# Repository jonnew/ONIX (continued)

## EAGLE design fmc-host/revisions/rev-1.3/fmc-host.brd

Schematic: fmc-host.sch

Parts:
AUX: 12226-8250-00FR; 12226-82X0-00XX
C1, C2, C47, C52, C57, C63, C85, C86, C94, C95, C99, C101, C102, C107, C109, C110, C111, C112, C113, C117, C118, C119: 10uF; 0805
C3, C4, C25, C26, C50, C51, C55, C56, C58, C59, C61, C62, C68, C73, C74, C81, C82, C90, C91, C114, C115, C116: 10nF; 0402
C5, C6, C12, C13, C14, C15, C16, C17, C18, C19, C20, C21, C22, C23, C24, C31, C32, C33, C34, C35, C36, C39, C42, C43, C44, C45, C46, C53, C54, C64, C65, C66, C71, C72, C75, C76, C77, C79, C80, C83, C87, C88, C92, C93, C96, C97, C98, C100, C103, C104, C105, C108, C123, C124, C125, C127, C128, C130, C131: 0.1uF; 0402
C7, C29, C30: 4.7nF; 0402
C8, C9, C10, C11, C27, C28, C37, C38, C48, C49, C67, C69, C70, C132, C133: 4.7uF; 1206
C40, C41: 47nF; 0402
C60, C78: 1uF; 0805
C84, C89, C120, C121, C122, C126, C129: 47uF; 1210
C106: 100pF; 0402
CLKI0, CLKI1: SMA002; MMCX-THRU
CLKO: SMA002; MMCX-THRU
D1, D2, D3: LED_0402; LED-0402
D4, D5: SESD0402X1UN-0020-090; 0402P-DFN
D6, D7, D8: BAR66; SOT23
D9: KDZ4.3B; SOD123
D10, D11: APFA3011-AK13/F; RGB_LED_SMD-6
F1, F2, F3: C014F-2; 1812
J6: PINHD-2X5_ESHF-SM; ESHF-105-01-L-D-SM-K-TR
J8: PINHD-2X8_SMD; JP2X8_SMD
J9: FMC_SINGLE_WIDTH_MODULE
J10: ASP-134488-01; FMC_HPC_MALE
L1, L2: 1008PS-472; 1008PS
L3, L4, L7, L8, L11, L12: BLM18KG601SN1D; 0603
L5, L6: SRNxx-101M; SRN6045TA
L9, L10: MPZ2012S102AT000; 0805
L13, L14, L15, L16, L17, L18: BLM15PX601SN1D; 0402; PARTNO BLM15PX601SN1D
LINKA: SMA002; MMCX-THRU
LINKB: SMA002; MMCX-THRU
Q1, Q2, Q3, Q4: SI1012R; SC75
R1: 1.6k; 0402
R2, R3: 3.9k; 0402
R4, R5, R29, R31, R45, R56, R61: 3k; 0402
R6, R7, R24, R25, R28, R30, R39, R40, R41, R42, R43, R44, R74, R79, R80, R81, R83, R84, R95, R96: 10k; 0402
R8, R9, R10, R11, R18, R19, R26, R27, R48, R49, R50, R51, R62, R63, R64, R65, R66, R67: 1k; 0402
R12, R13, R22, R23, R93: 165k; 0402
R14, R15, R16, R17, R20, R21: 150,0.25W; 0603
R32, R33: 60 1%; 0402
R34, R35, R46, R47: 49.9; 0402
R36, R37, R38: 100; 0402
R52, R54, R57, R59: DNP; 0402
R53, R55, R58, R60, R78, R82: 0; 0402
R68, R69, R70, R71: 2.2k; RN2X8-1506
R72, R73, R91, R92: 2k; 0402
R75, R76: 3.16k; 0402
R77: 649k; 0402
R85: 15k; 0402
R86, R88, R90: 4.7k; 0402
R87, R89: 43k; 0402
R94: 178k; 0402
R97, R98: 73.2k; 0402
S1, S2: CHS-01TA; DIP01-SMD-GULL
S3: CHS-02TB
SJ1, SJ2: SJ2_0201; SJ_2_0201
TP1, TP2, TP4, TP5, TP6, TP7, TP11, TP12, TP13, TP14, TP15, TP16: TPB1,27; B1,27
TP3, TP8, TP9, TP10, TP17, TP18: TPB2,54; B2,54
U1: NC7WZ07P6X; SC70
U2: SN65LVDS9638DGN; MSOP-8-PAD-3X3
U3: FIN1032MTCX; TSSOP-16
U4: LTC2875_DFN; DFN83X3
U5, U6: ADCMP600; SOT-23-5
U7, U8, U9: ADG1434YCPZ; QFN20-4X4MM
U10, U11: DS90UB914A-Q1; WQFN48-7.4X7.4
U12: DS91M040; WQFN32-5X5
U13: AD5766BCPZ-RL7; CP_40_7
U14: MCP47FEB02A0-E/ST; TSSOP-8
U15: LM4132AMF-2.5/NOPBCT-ND; SOT-23-5
U16: AD7617BSTZ; ST_80_2
U17: AD5142BCPZ10; CP_16_27-L
U18: LTM4622A; BGA_5X5_625X625
U19, U20: TPS7A49; PVSON-N8+4-3X3
U21: TPS7A30; PVSON-N8+4-3X3
U22: 24AA64ST; TSSOP8
U23: LTM8049_BGA; LTM8049
X2, X3: OE-LOGO_7X5; OE-LOGO-7X5

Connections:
!ADC_CS: J10.H13 (LA07_P), U16.63 (!CS)
!ADC_RESET: C106.1, J10.F10 (HA08_P), R81.2, U16.36 (!RESET)
!AIN_AOUT_EN: J10.J19 (HA18_N), U7.18 (!EN), U8.18 (!EN), U9.18 (!EN)
!DAC_CS: J10.J16 (HA14_N), U13.8 (!CS)
!DAC_RESET: J10.F14 (HA12_N), U13.3 (!RESET)
!LINK_PWR_ADJ_CS: J10.F38 (HB20_N), U17.14 (!CS)
!LINK_PWR_ADJ_RESET: J10.E37 (HB21_N), U17.16 (!RESET)
$N1: D8.3 (COMM), F2.2, R5.2, R15.2, R17.2, R21.2, R35.1
$N2: D6.3 (COMM), F3.2, U1.4 (OUT2), U1.6 (OUT1)
$N3: D7.3 (COMM), F1.2, R4.2, R14.2, R16.2, R20.2, R34.1
+1V8: C73.2, C74.2, C76.2, C77.2, C81.2, C82.2, C87.2, C88.2, C90.2, C91.2, C96.2, C97.2, C129.2, C130.2, C131.2, J10.E39 (VADJ), J10.F40 (VADJ), J10.G39 (VADJ), J10.H40 (VADJ), L3.2, L4.2, L7.2, L8.2, L11.1, L12.1, R28.1, R30.1, R52.1, R54.1, R57.1, R59.1, TP16.TP, U10.3 (VDDSSCG), U10.17 (VDDD), U10.36 (VDDR), U11.3 (VDDSSCG), U11.17 (VDDD), U11.36 (VDDR)
+3V3: C15.2, C23.1, C24.1, C29.1, C30.1, C35.1, C36.1, C39.1, C45.2, C46.2, C50.2, C51.2, C55.2, C56.2, C60.2, C61.2, C62.2, C64.2, C65.2, C66.2, C68.2, C69.2, C70.2, C79.2, C83.2, C86.2, C104.2, C107.2, C108.2, C110.2, C126.2, C127.2, C128.2, C132.1, C133.1, J10.C39 (3P3V1), J10.D36 (3P3V2), J10.D38 (3P3V3), J10.D40 (3P3V4), R6.1, R7.1, R41.2, R42.2, R43.2, R44.2, R48.2, R49.2, R50.2, R51.2, R72.2, R73.2, R78.1, R79.1, R80.1, R81.1, R95.2, R96.2, S1.2, S2.2, TP11.TP, U1.5 (VCC), U2.1 (VCC), U3.4 (EN), U3.16 (VCC), U4.3 (VCC), U5.5 (V+), U6.5 (V+), U10.7 (VDDIO3), U10.20 (VDDIO2), U10.29 (VDDIO1), U11.7 (VDDIO3), U11.20 (VDDIO2), U11.29 (VDDIO1), U12.11 (VDD), U12.12 (VDD), U12.29 (VDD), U12.30 (VDD), U13.4 (VLOGIC), U14.1 (VDD), U14.2 (REFA), U16.49 (VDRIVE), U17.9 (VDD), U17.10 (VLOGIC), U17.15 (INDEP), U23.A5 (VIN1), U23.A6 (VIN1), U23.A7 (VIN1), U23.B7 (RUN1), U23.K7 (RUN2), U23.L5 (VIN2), U23.L6 (VIN2), U23.L7 (VIN2)
+5V_AN: C47.2, C52.2, C57.2, C63.2, C67.1, C71.2, C72.2, C75.2, C80.2, C100.2, C101.2, L13.1, R1.2, TP1.TP, U13.28 (AVCC), U15.3 (EN), U15.4 (VIN), U16.6 (VCC), U16.15 (VCC), U16.30 (VCC), U16.71 (VCC)
+12V: AUX.1, AUX.26, C109.2, C120.2, C123.2, C124.2, J10.C35 (12P0V1), J10.C37 (12P0V2), R56.2, R61.2, TP12.TP, U18.A2 (VIN), U18.B3 (VIN), U18.D3 (VIN), U18.E2 (VIN)
+13V_AN: C12.2, C13.2, C14.2, C98.2, C99.2, L14.1, R2.2, TP2.TP, U7.13 (V+), U8.13 (V+), U9.13 (V+), U13.26 (AVDD)
+15V: C121.2, L16.2, L17.2, R93.1, U23.A1 (VOUT1P), U23.A2 (VOUT1P), U23.B1 (VOUT1P), U23.B2 (VOUT1P)
-13V_AN: C20.2, C21.2, C22.2, C92.2, C95.2, L15.1, R3.2, TP4.TP, U7.3 (V-), U7.PAD (V-), U8.3 (V-), U8.PAD (V-), U9.3 (V-), U9.PAD (V-), U13.6 (AVSS), U13.PAD (AVSS)
-15V: C122.1, L18.2, R94.1, U23.G1 (VOUT2N), U23.G2 (VOUT2N), U23.H1 (VOUT2N), U23.H2 (VOUT2N), U23.J2 (VOUT2N)
ADC_BUSY: J10.J12 (HA11_P), U16.67 (BUSY)
ADC_CONVST: J10.K13 (HA10_P), U16.68 (CONVST)
ADC_MISO_A: J10.K11 (HA06_N), U16.57 (DB12/SDOA)
ADC_MISO_B: J10.J10 (HA07_N), U16.56 (DB11/SDOB)
ADC_MOSI: J10.K10 (HA06_P), U16.55 (DB10/SDI)
ADC_SCLK: J10.J13 (HA11_N), U16.62 (SCLK/!RD)
ADDR0: J10.C27 (LA27_N), R95.1, S3.4
ADDR1: J10.C26 (LA27_P), R96.1, S3.3
AGND: AUX.13, AUX.14, C12.1, C13.1, C14.1, C20.1, C21.1, C22.1, C47.1, C52.1, C57.1, C63.1, C67.2, C71.1, C72.1, C75.1, C78.1, C80.1, C85.1, C92.1, C93.1, C94.1, C95.1, C98.1, C99.1, C100.1, C101.1, D1.C, D2.C, D3.A, R68.C2, R68.C4, R68.C6, R68.C7, R69.C1, R69.C3, R69.C5, R69.C6, R69.C7, R69.C8, R70.C2, R70.C3, R70.C5, R70.C7, R71.C1, R71.C2, R71.C3, R71.C4, R71.C6, R71.C8, R82.1, TP3.TP, U7.4 (GND), U8.4 (GND), U9.4 (GND), U13.10 (AGND), U13.20 (NIC), U13.23 (N0), U13.24 (N1), U13.25 (NIC), U13.29 (AGND), U13.31 (NIC), U15.2 (GND), U16.5 (AGND), U16.16 (AGND), U16.29 (AGND), U16.32 (REFGND), U16.34 (REFINOUTGND), U16.69 (REGGND), U16.72 (AGND)
AINA0: R68.C1, U9.20 (S1A)
AINA1: R68.C3, U9.7 (S2A)
AINA2: R68.C5, U9.10 (S3A)
AINA3: R68.C8, U9.16 (S4A)
AINA4: R69.C2, U8.7 (S2A)
AINA5: R69.C4, U8.20 (S1A)
AINB0: R70.C8, U7.16 (S4A)
AINB1: R70.C6, U7.10 (S3A)
AINB2: R70.C4, U7.7 (S2A)
AINB3: R70.C1, U7.20 (S1A)
AINB4: R71.C7, U8.16 (S4A)
AINB5: R71.C5, U8.10 (S3A)
AIN_AOUT0: J10.H19 (LA15_P), U7.19 (IN1)
AIN_AOUT1: J10.G19 (LA16_N), U7.8 (IN2)
AIN_AOUT2: J10.H20 (LA15_N), U7.9 (IN3)
AIN_AOUT3: J10.J18 (HA18_P), U7.17 (IN4)
AIN_AOUT4: J10.E18 (HA20_P), U8.19 (IN1)
AIN_AOUT5: J10.J9 (HA07_P), U8.8 (IN2)
AIN_AOUT6: J10.G10 (LA03_N), U8.9 (IN3)
AIN_AOUT7: J10.F17 (HA15_N), U8.17 (IN4)
AIN_AOUT8: J10.F11 (HA08_N), U9.19 (IN1)
AIN_AOUT9: J10.D11 (LA05_P), U9.8 (IN2)
AIN_AOUT10: J10.E12 (HA13_P), U9.9 (IN3)
AIN_AOUT11: J10.H10 (LA04_P), U9.17 (IN4)
AIO_0: AUX.25, U7.1 (D1)
AIO_1: AUX.12, U7.6 (D2)
AIO_2: AUX.24, U7.15 (D4)
AIO_3: AUX.11, U7.11 (D3)
AIO_4: AUX.23, U8.15 (D4)
AIO_5: AUX.10, U8.11 (D3)
AIO_6: AUX.22, U8.6 (D2)
AIO_7: AUX.9, U8.1 (D1)
AIO_8: AUX.21, U9.15 (D4)
AIO_9: AUX.8, U9.11 (D3)
AIO_10: AUX.20, U9.6 (D2)
AIO_11: AUX.7, U9.1 (D1)
AOUT0: U7.2 (S1B), U13.32 (VOUT0)
AOUT1: U7.5 (S2B), U13.33 (VOUT1)
AOUT2: U7.12 (S3B), U13.34 (VOUT2)
AOUT3: U7.14 (S4B), U13.35 (VOUT3)
AOUT4: U8.2 (S1B), U13.36 (VOUT4)
AOUT5: U8.5 (S2B), U13.37 (VOUT5)
AOUT6: U8.14 (S4B), U13.38 (VOUT6)
AOUT7: U8.12 (S3B), U13.39 (VOUT7)
AOUT8: U9.12 (S3B), U13.12 (VOUT8)
AOUT9: U9.14 (S4B), U13.13 (VOUT9)
AOUT10: U9.5 (S2B), U13.14 (VOUT10)
AOUT11: U9.2 (S1B), U13.15 (VOUT11)
CAN_N: R33.2, SJ1.2, U4.6 (CANL)
CAN_P: R32.2, SJ2.2, U4.7 (CANH)
CAN_RX: J10.K8 (HA02_N), U4.4 (RXD)
CAN_TX: J10.K7 (HA02_P), U4.1 (TXD)
CLKIN0: J10.D21 (LA17_N_CC), TP7.TP, U5.1 (OUT)
CLKIN1: J10.E19 (HA20_N), TP6.TP, U6.1 (OUT)
CLKIN_TERM0: J10.K19 (HA21_P), R26.1
CLKIN_TERM1: J10.K17 (HA17_N_CC), R27.1
CLKIN_VBIAS_SCL: J10.J21 (HA22_P), R73.1, U14.7 (SCL)
CLKIN_VBIAS_SDA: J10.K20 (HA21_N), R72.1, U14.8 (SDA)
CLKOUT: J10.D20 (LA17_P_CC), U1.1 (IN3), U1.3 (IN2)
DAC_MISO: J10.K16 (HA17_P_CC), U13.9 (MISO)
DAC_MOSI: J10.H14 (LA07_N), U13.5 (MOSI)
DAC_MUX: TP15.TP, U13.27 (MUX_OUT)
DAC_SCLK: J10.J15 (HA14_P), U13.7 (SCLK)
DEBUG0: J8.2, J10.C10 (LA06_P)
DEBUG1: J8.4, J10.C11 (LA06_N)
DEBUG2: J8.6, J10.D14 (LA09_P)
DEBUG3: J8.8, J10.C14 (LA10_P)
DEBUG4: J8.10, J10.D15 (LA09_N)
DEBUG5: J8.12, J10.C15 (LA10_N)
DEBUG6: J8.14, J10.C18 (LA14_P)
DEBUG7: J8.16, J10.C19 (LA14_N)
DES_A_D0: J10.F34 (HB16_P), U11.24 (ROUT0)
DES_A_D1: J10.K35 (HB14_N), U11.23 (ROUT1)
DES_A_D2: J10.J34 (HB15_N), U11.22 (ROUT2)
DES_A_D3: J10.K34 (HB14_P), U11.21 (ROUT3)
DES_A_D4: J10.E33 (HB19_P), U11.19 (ROUT4)
DES_A_D5: J10.J33 (HB15_P), U11.18 (ROUT5)
DES_A_D6: J10.F32 (HB12_N), U11.16 (ROUT6)
DES_A_D7: J10.E31 (HB13_N), U11.15 (ROUT7)
DES_A_D8: J10.K32 (HB10_N), U11.14 (ROUT8)
DES_A_D9: J10.F31 (HB12_P), U11.13 (ROUT9)
DES_A_D10: J10.J31 (HB11_N), U11.12 (ROUT10)
DES_A_D11: J10.K31 (HB10_P), U11.11 (ROUT11)
DES_A_GPIO0: J10.J37 (HB18_N), U11.28 (GPIO0)
DES_A_GPIO1: J10.K37 (HB17_P_CC), U11.27 (GPIO1)
DES_A_GPIO2: J10.J36 (HB18_P), U11.26 (GPIO2)
DES_A_GPIO3: J10.E34 (HB19_N), U11.25 (GPIO3)
DES_A_HSYNC: J10.E30 (HB13_P), U11.10 (HSYNC)
DES_A_LEDG: J10.F28 (HB08_P), R67.2
DES_A_LOCK: J10.E27 (HB09_P), R63.2, U11.48 (LOCK)
DES_A_PASS: J10.J28 (HB07_N), R65.2, U11.47 (PASS)
DES_A_PCLK: J10.K28 (HB06_P_CC), U11.8 (PCLK)
DES_A_PDN: J10.F35 (HB16_N), R11.2
DES_A_SCL: J10.F29 (HB08_N), R49.1, U11.2 (SCL)
DES_A_SDA\: J10.E28 (HB09_N), R51.1, U11.1 (SDA)
DES_A_VSYNC: J10.J30 (HB11_P), U11.9 (VSYNC)
DES_B_D0: J10.H29 (LA24_N), U10.24 (ROUT0)
DES_B_D1: J10.H28 (LA24_P), U10.23 (ROUT1)
DES_B_D2: J10.G28 (LA25_N), U10.22 (ROUT2)
DES_B_D3: J10.G27 (LA25_P), U10.21 (ROUT3)
DES_B_D4: J10.D27 (LA26_N), U10.19 (ROUT4)
DES_B_D5: J10.D26 (LA26_P), U10.18 (ROUT5)
DES_B_D6: J10.H26 (LA21_N), U10.16 (ROUT6)
DES_B_D7: J10.G25 (LA22_N), U10.15 (ROUT7)
DES_B_D8: J10.H25 (LA21_P), U10.14 (ROUT8)
DES_B_D9: J10.D24 (LA23_N), U10.13 (ROUT9)
DES_B_D10: J10.G24 (LA22_P), U10.12 (ROUT10)
DES_B_D11: J10.D23 (LA23_P), U10.11 (ROUT11)
DES_B_GPIO0: J10.H32 (LA28_N), U10.28 (GPIO0)
DES_B_GPIO1: J10.G31 (LA29_N), U10.27 (GPIO1)
DES_B_GPIO2: J10.H31 (LA28_P), U10.26 (GPIO2)
DES_B_GPIO3: J10.G30 (LA29_P), U10.25 (GPIO3)
DES_B_HSYNC\: J10.H23 (LA19_N), U10.10 (HSYNC)
DES_B_LEDG: J10.G21 (LA20_P), R66.2
DES_B_LOCK: J10.J22 (HA22_N), R62.2, U10.48 (LOCK)
DES_B_PASS: J10.K22 (HA23_P), R64.2, U10.47 (PASS)
DES_B_PCLK: J10.C22 (LA18_P_CC), U10.8 (PCLK)
DES_B_PDN: J10.G33 (LA31_P), R10.2
DES_B_SCL: J10.G22 (LA20_N), R48.1, U10.2 (SCL)
DES_B_SDA: J10.H22 (LA19_P), R50.1, U10.1 (SDA)
DES_B_VSYNC: J10.K23 (HA23_N), U10.9 (VSYNC)
DI_VBIAS0: R24.1, U14.3 (VOUT0)
DI_VBIAS1: R25.1, U14.4 (VOUT1)
DOUTP_F_A: C43.2, D5.C, L2.2, LINKA.SIG (1), R9.2
DOUTP_F_B: C42.2, D4.C, L1.2, LINKB.SIG (1), R8.2
GND: AUX.PAD1, AUX.PAD2, C1.1, C2.1, C3.1, C4.1, C5.1, C6.1, C7.2, C8.1, C9.1, C10.1, C11.1, C15.1, C16.2, C17.2, C18.2, C19.2, C23.2, C24.2, C25.1, C26.1, C27.1, C28.1, C29.2, C30.2, C31.1, C32.1, C33.2, C34.2, C35.2, C36.2, C37.1, C38.1, C39.2, C44.1, C45.1, C46.1, C48.1, C49.1, C50.1, C51.1, C53.1, C54.1, C55.1, C56.1, C58.1, C59.1, C60.1, C61.1, C62.1, C64.1, C65.1, C66.1, C68.1, C69.1, C70.1, C73.1, C74.1, C76.1, C77.1, C79.1, C81.1, C82.1, C83.1, C84.1, C86.1, C87.1, C88.1, C89.1, C90.1, C91.1, C96.1, C97.1, C102.1, C103.1, C104.1, C105.1, C106.2, C107.1, C108.1, C109.1, C110.1, C111.1, C112.1, C113.1, C114.2, C115.2, C116.2, C117.1, C118.1, C119.1, C120.1, C121.1, C122.2, C123.1, C124.1, C125.1, C126.1, C127.1, C128.1, C129.1, C130.1, C131.1, C132.2, C133.2, CLKI0.GND@1 (2), CLKI0.GND@2 (2), CLKI0.GND@3 (2), CLKI0.GND@4 (2), CLKI1.GND@1 (2), CLKI1.GND@2 (2), CLKI1.GND@3 (2), CLKI1.GND@4 (2), CLKO.GND@1 (2), CLKO.GND@2 (2), CLKO.GND@3 (2), CLKO.GND@4 (2), D4.A, D5.A, D6.1 (A), D7.1 (A), D8.1 (A), D9.A, D10.3 (C), D10.5 (C), D10.6 (C), D11.3 (C), D11.5 (C), D11.6 (C), J8.1, J8.3, J8.5, J8.7, J8.9, J8.11, J8.13, J8.15, J10.A1 (GND), J10.A4 (GND), J10.A5 (GND), J10.A8 (GND), J10.A9 (GND), J10.A12 (GND), J10.A13 (GND), J10.A16 (GND), J10.A17 (GND), J10.A20 (GND), J10.A21 (GND), J10.A24 (GND), J10.A25 (GND), J10.A28 (GND), J10.A29 (GND), J10.A32 (GND), J10.A33 (GND), J10.A36 (GND), J10.A37 (GND), J10.A40 (GND), J10.B2 (GND), J10.B3 (GND), J10.B6 (GND), J10.B7 (GND), J10.B10 (GND), J10.B11 (GND), J10.B14 (GND), J10.B15 (GND), J10.B18 (GND), J10.B19 (GND), J10.B22 (GND), J10.B23 (GND), J10.B26 (GND), J10.B27 (GND), J10.B30 (GND), J10.B31 (GND), J10.B34 (GND), J10.B35 (GND), J10.B38 (GND), J10.B39 (GND), J10.C1 (GND), J10.C4 (GND), J10.C5 (GND), J10.C8 (GND), J10.C9 (GND), J10.C12 (GND), J10.C13 (GND), J10.C16 (GND), J10.C17 (GND), J10.C20 (GND), J10.C21 (GND), J10.C24 (GND), J10.C25 (GND), J10.C28 (GND), J10.C29 (GND), J10.C32 (GND), J10.C33 (GND), J10.C34 (GA0), J10.C36 (GND), J10.C38 (GND), J10.C40 (GND), J10.D2 (GND), J10.D3 (GND), J10.D6 (GND), J10.D7 (GND), J10.D10 (GND), J10.D13 (GND), J10.D16 (GND), J10.D19 (GND), J10.D22 (GND), J10.D25 (GND), J10.D28 (GND), J10.D35 (GA1), J10.D37 (GND), J10.D39 (GND), J10.E1 (GND), J10.E4 (GND), J10.E5 (GND), J10.E8 (GND), J10.E11 (GND), J10.E14 (GND), J10.E17 (GND), J10.E20 (GND), J10.E23 (GND), J10.E26 (GND), J10.E29 (GND), J10.E32 (GND), J10.E35 (GND), J10.E38 (GND), J10.E40 (GND), J10.F2 (GND), J10.F3 (GND), J10.F6 (GND), J10.F9 (GND), J10.F12 (GND), J10.F15 (GND), J10.F18 (GND), J10.F21 (GND), J10.F24 (GND), J10.F27 (GND), J10.F30 (GND), J10.F33 (GND), J10.F36 (GND), J10.F39 (GND), J10.G1 (GND), J10.G4 (GND), J10.G5 (GND), J10.G8 (GND), J10.G11 (GND), J10.G14 (GND), J10.G17 (GND), J10.G20 (GND), J10.G23 (GND), J10.G26 (GND), J10.G29 (GND), J10.G32 (GND), J10.G35 (GND), J10.G38 (GND), J10.G40 (GND), J10.H3 (GND), J10.H6 (GND), J10.H9 (GND), J10.H12 (GND), J10.H15 (GND), J10.H18 (GND), J10.H21 (GND), J10.H24 (GND), J10.H27 (GND), J10.H30 (GND), J10.H33 (GND), J10.H36 (GND), J10.H39 (GND), J10.J1 (GND), J10.J4 (GND), J10.J5 (GND), J10.J8 (GND), J10.J11 (GND), J10.J14 (GND), J10.J17 (GND), J10.J20 (GND), J10.J23 (GND), J10.J26 (GND), J10.J29 (GND), J10.J32 (GND), J10.J35 (GND), J10.J38 (GND), J10.J40 (GND), J10.K2 (GND), J10.K3 (GND), J10.K6 (GND), J10.K9 (GND), J10.K12 (GND), J10.K15 (GND), J10.K18 (GND), J10.K21 (GND), J10.K24 (GND), J10.K27 (GND), J10.K30 (GND), J10.K33 (GND), J10.K36 (GND), J10.K39 (GND), LINKA.GND@1 (2), LINKA.GND@2 (2), LINKA.GND@3 (2), LINKA.GND@4 (2), LINKB.GND@1 (2), LINKB.GND@2 (2), LINKB.GND@3 (2), LINKB.GND@4 (2), Q1.2 (S), Q2.2 (S), Q3.2 (S), Q4.2 (S), R4.1, R5.1, R12.1, R13.1, R22.1, R23.1, R29.2, R31.2, R39.2, R40.2, R45.1, R46.2, R47.2, R53.2, R55.2, R58.2, R60.2, R77.2, R82.2, R83.2, R84.2, R86.1, R88.1, R90.1, R97.2, R98.2, S3.1, S3.2, TP8.TP, TP9.TP, TP10.TP, TP17.TP, TP18.TP, U1.2 (GND), U2.4 (GND), U2.PAD (GND), U3.8 (GND), U3.12 (!EN), U4.2 (GND), U4.PAD (GND), U5.2 (V-), U6.2 (V-), U10.43 (RES), U10.44 (TESTEN), U10.46 (SEL), U10.49 (DAP), U11.43 (RES), U11.44 (TESTEN), U11.46 (SEL), U11.49 (DAP), U12.31 (GND), U12.PAD (GND), U13.2 (DGND), U14.5 (AVSS), U14.6 (LAT/HVC), U16.37 (SEQEN), U16.38 (HW_RNGSEL1), U16.39 (HW_RNGSEL0), U16.41 (DB0), U16.42 (DB1), U16.43 (DB2), U16.44 (DB3), U16.46 (DB5/CRCEN), U16.47 (DB6), U16.48 (DB7), U16.50 (DGND), U16.51 (REGGNDD), U16.53 (DB8), U16.54 (DB9), U16.58 (DB13/OS0), U16.59 (DB14/OS1), U16.60 (DB15/OS2), U16.61 (WR!/BURST), U16.64 (CHSEL0), U16.65 (CHSEL1), U16.66 (CHSEL2), U17.1 (GND), U17.3 (W1), U17.5 (VSS), U17.7 (W2), U17.PAD (VSS), U18.B5 (GND), U18.C1 (GND), U18.C2 (GND), U18.C5 (SYNC/MODE), U18.D5 (GND), U19.3 (NC), U19.4 (GND), U19.PAD1 (PAD), U19.PAD2 (PAD), U19.PAD3 (PAD), U19.PAD4 (PAD), U19.PAD5 (PAD), U20.3 (NC), U20.4 (GND), U20.PAD1 (PAD), U20.PAD2 (PAD), U20.PAD3 (PAD), U20.PAD4 (PAD), U20.PAD5 (PAD), U21.3 (NC), U21.4 (GND), U21.PAD1 (PAD), U21.PAD2 (PAD), U21.PAD3 (PAD), U21.PAD4 (PAD), U21.PAD5 (PAD), U22.1 (A0), U22.2 (A1), U22.3 (A2), U22.4 (GND), U22.7 (WP), U23.A3 (GND), U23.A4 (GND), U23.B3 (GND), U23.B4 (GND), U23.B5 (GND), U23.B6 (GND), U23.C2 (VOUT1N), U23.C3 (GND), U23.C4 (GND), U23.C5 (GND), U23.C6 (GND), U23.D1 (VOUT1N), U23.D2 (VOUT1N), U23.D3 (GND), U23.D4 (GND), U23.D5 (GND), U23.D7 (SYNC1), U23.E1 (VOUT1N), U23.E2 (VOUT1N), U23.E3 (GND), U23.E4 (GND), U23.E5 (GND), U23.F1 (GND), U23.F2 (GND), U23.F5 (GND), U23.F6 (GND), U23.F7 (GND), U23.G3 (GND), U23.G4 (GND), U23.G5 (GND), U23.H3 (GND), U23.H4 (GND), U23.H5 (GND), U23.J3 (GND), U23.J4 (GND), U23.J5 (GND), U23.J6 (GND), U23.K1 (VOUT2P), U23.K2 (VOUT2P), U23.K3 (GND), U23.K4 (GND), U23.K5 (GND), U23.K6 (GND), U23.L1 (VOUT2P), U23.L2 (VOUT2P), U23.L3 (GND), U23.L4 (GND)
LINK_A_PWR_EN: J10.H37 (LA32_P), R84.1, U18.B2 (RUN2)
LINK_B_PWR_EN: J10.K38 (HB17_N_CC), R83.1, U18.D2 (RUN1)
LINK_PWR_ADJ_MISO: J10.F37 (HB20_P), U17.13 (MISO)
LINK_PWR_ADJ_MOSI: J10.E36 (HB21_P), U17.12 (MOSI)
LINK_PWR_ADJ_SCLK: J10.H38 (LA32_N), U17.11 (SCLK)
LVDS_DIN0: J10.J2 (CLK1_C2M_P), U3.3 (AOUT)
LVDS_DIN0_N: AUX.4, R36.1, U3.1 (A-)
LVDS_DIN0_P: AUX.17, R36.2, U3.2 (A+)
LVDS_DIN1: J10.H5 (CLK0_M2C_N), U3.5 (BOUT)
LVDS_DIN1_N: AUX.16, R37.1, U3.7 (B-)
LVDS_DIN1_P: AUX.3, R37.2, U3.6 (B+)
LVDS_DIN2: J10.H4 (CLK0_M2C_P), U3.11 (COUT)
LVDS_DIN2_N: R38.1, SJ2.1, U3.9 (C-)
LVDS_DIN2_P: R38.2, SJ1.1, U3.10 (C+)
LVDS_DOUT0: J10.J3 (CLK1_C2M_N), U2.2 (AIN)
LVDS_DOUT0_N: AUX.19, U2.7 (AOUT-)
LVDS_DOUT0_P: AUX.6, U2.8 (AOUT+)
LVDS_DOUT1: J10.K4 (CLK1_M2C_P), U2.3 (BIN)
LVDS_DOUT1_N: AUX.18, U2.5 (BOUT-)
LVDS_DOUT1_P: AUX.5, U2.6 (BOUT+)
MLDVS_EN: J10.H8 (LA02_N), U12.10 (MDE)
MLDVS_RO0: J10.G2 (CLK0_C2M_P), U12.1 (RO0)
MLDVS_RO1: J10.E3 (HA01_N_CC), U12.3 (RO1)
MLDVS_RO2: J10.G7 (LA00_N_CC), U12.5 (RO2)
MLDVS_RO3: J10.F4 (HA00_P_CC), U12.7 (RO3)
MLVDS_CLK_0_N: J6.9, U12.24 (B0)
MLVDS_CLK_0_P: J6.10, U12.23 (A0)
MLVDS_CLK_1_N: J6.7, U12.22 (B1)
MLVDS_CLK_1_P: J6.8, U12.21 (A1)
MLVDS_CLK_2_N: J6.3, U12.20 (B2)
MLVDS_CLK_2_P: J6.4, U12.19 (A2)
MLVDS_CLK_3_N: J6.1, U12.18 (B3)
MLVDS_CLK_3_P: J6.2, U12.17 (A3)
MLVDS_DE_!RE0: J10.F7 (HA04_P), U12.25 (DE0), U12.26 (!RE0)
MLVDS_DE_!RE1: J10.E7 (HA05_N), U12.27 (DE1), U12.28 (!RE1)
MLVDS_DE_!RE2: J10.H7 (LA02_P), U12.13 (!RE2), U12.14 (DE2)
MLVDS_DE_!RE3: J10.F8 (HA04_N), U12.15 (!RE3), U12.16 (DE3)
MLVDS_DI0: J10.G3 (CLK0_C2M_N), U12.2 (DI0)
MLVDS_DI1: J10.E2 (HA01_P_CC), U12.4 (DI1)
MLVDS_DI2: J10.G6 (LA00_P_CC), U12.6 (DI2)
MLVDS_DI3: J10.F5 (HA00_N_CC), U12.8 (DI3)
unnamed: Q2.1 (G), R11.1, R13.2
unnamed: Q3.3 (D), R14.1, R16.1, R20.1
unnamed: R34.2, U5.3 (+IN)
unnamed: L1.1, L5.2, R8.1, R18.2
unnamed: R76.1, U18.A4 (FB2)
unnamed: CLKI1.SIG (1), F2.1
unnamed: Q4.3 (D), R15.1, R17.1, R21.1
unnamed: C103.2, U18.A3 (TRACK/SS2)
unnamed: R98.1, U23.G7 (RT2)
unnamed: R75.1, U18.E4 (FB1)
unnamed: CLKI0.SIG (1), F1.1
unnamed: C105.2, U18.E3 (TRACK/SS1)
unnamed: R45.2, U4.8 (RS)
unnamed: CLKO.SIG (1), F3.1
unnamed: C117.2, L16.1, U19.5 (EN), U19.8 (IN)
unnamed: D11.4 (A), R67.1
unnamed: R97.1, U23.E7 (RT1)
unnamed: C16.1, R24.2, U5.4 (-IN)
unnamed: R35.2, U6.3 (+IN)
unnamed: C17.1, R25.2, U6.4 (-IN)
unnamed: L2.1, L6.2, R9.1, R19.2
unnamed: C11.2, C19.1, L6.1, L10.2, R19.1
unnamed: R70.1, U16.79 (V3B)
unnamed: C9.2, C18.1, L5.1, L9.2, R18.1
unnamed: R94.2, U23.J1 (FBX2)
unnamed: D10.4 (A), R66.1
unnamed: C43.1, U11.41 (RIN0+)
unnamed: C41.1, U11.42 (RIN0-)
unnamed: R93.2, U23.C1 (FBX1)
unnamed: AUX.2, SJ2.COM
unnamed: AUX.15, SJ1.COM
unnamed: C41.2, R47.1
unnamed: C114.1, U19.6 (NR/SS)
unnamed: Q4.1 (G), R23.2, R27.2
unnamed: U23.E6 (CLKOUT1), U23.H7 (SYNC2)
unnamed: D3.C, R3.1
unnamed: Q3.1 (G), R22.2, R26.2
unnamed: C42.1, U10.41 (RIN0+)
unnamed: R70.2, U16.80 (V3BGND)
unnamed: R85.1, R86.2, U19.2 (FB)
unnamed: C7.1, R32.1, R33.1, U4.5 (SPLIT)
unnamed: C118.2, L17.1, U20.5 (EN), U20.8 (IN)
unnamed: C115.1, U20.6 (NR/SS)
unnamed: D11.1 (A), R63.1
unnamed: D11.2 (A), R65.1
unnamed: C40.1, U10.42 (RIN0-)
unnamed: R87.1, R88.2, U20.2 (FB)
unnamed: D1.A, R1.1
unnamed: C119.2, L18.1, U21.5 (EN), U21.8 (IN)
unnamed: C116.1, U21.6 (NR/SS)
unnamed: R89.1, R90.2, U21.2 (FB)
unnamed: R80.2, U16.45 (DB4/!SER1WR)
unnamed: R68.1, U16.28 (V0A)
unnamed: R79.2, U16.40 (SER/!PAR)
unnamed: C85.2, U16.31 (REFCAP)
unnamed: R68.2, U16.27 (V0AGND)
unnamed: D2.A, R2.1
unnamed: C102.2, U16.52 (REGCAPD)
unnamed: R70.8, U16.73 (V0B)
unnamed: C94.2, U16.70 (REGCAP)
unnamed: R78.2, U16.35 (REFSEL)
unnamed: R71.7, U16.2 (V4B)
unnamed: R71.1, U16.10 (V7BGND)
unnamed: R70.7, U16.74 (V0BGND)
unnamed: R70.6, U16.75 (V1B)
unnamed: R70.5, U16.76 (V1BGND)
unnamed: R70.4, U16.77 (V2B)
unnamed: R70.3, U16.78 (V2BGND)
unnamed: R68.3, U16.26 (V1A)
unnamed: R68.4, U16.25 (V1AGND)
unnamed: R68.5, U16.24 (V2A)
unnamed: R68.6, U16.23 (V2AGND)
unnamed: R68.8, U16.22 (V3A)
unnamed: R68.7, U16.21 (V3AGND)
unnamed: R69.2, U16.19 (V4A)
unnamed: R69.1, U16.20 (V4AGND)
unnamed: R69.4, U16.17 (V5A)
unnamed: R69.3, U16.18 (V5AGND)
unnamed: R69.5, U16.14 (V6A)
unnamed: R69.6, U16.13 (V6AGND)
unnamed: R69.7, U16.12 (V7A)
unnamed: R69.8, U16.11 (V7AGND)
unnamed: C40.2, R46.1
unnamed: R71.8, U16.1 (V4BGND)
unnamed: R71.5, U16.4 (V5B)
unnamed: R71.6, U16.3 (V5BGND)
unnamed: R71.4, U16.7 (V6B)
unnamed: R71.3, U16.8 (V6BGND)
unnamed: R71.2, U16.9 (V7B)
unnamed: R52.2, R53.1, U10.35 (IDX0)
unnamed: R57.2, R58.1, U10.34 (IDX1)
unnamed: Q1.1 (G), R10.1, R12.2
unnamed: D10.1 (A), R62.1
unnamed: D10.2 (A), R64.1
unnamed: R75.2, U17.2 (A1)
unnamed: R76.2, U17.6 (A2)
unnamed: R77.1, U18.C4 (FREQ)
unnamed: R44.1, U11.4 (OSS_SEL)
unnamed: R42.1, U11.5 (OEN)
unnamed: R40.1, S2.1, U11.6 (BISTEN)
unnamed: R30.2, R31.1, U11.37 (MODE)
unnamed: R54.2, R55.1, U11.35 (IDX0)
unnamed: R59.2, R60.1, U11.34 (IDX1)
unnamed: C111.2, L13.2, R85.2, U19.1 (OUT)
unnamed: C112.2, L14.2, R87.2, U20.1 (OUT)
unnamed: C113.2, L15.2, R89.2, U21.1 (OUT)
unnamed: C93.2, R74.1, U16.33 (REFINOUT)
unnamed: C2.2, Q2.3 (D), R7.2, U11.30 (PDN)
unnamed: C1.2, Q1.3 (D), R6.2, U10.30 (PDN)
unnamed: R43.1, U10.4 (OSS_SEL)
unnamed: R41.1, U10.5 (OEN)
unnamed: R39.1, S1.1, U10.6 (BISTEN)
unnamed: R28.2, R29.1, U10.37 (MODE)
SCL: J10.C30 (SCL), R91.1, U22.6 (SCL)
SDA: J10.C31 (SDA), R92.1, U22.5 (SDA)
TDI-TDO: J10.D30 (TDI), J10.D31 (TDO)
VAUX: C125.2, J10.D32 (3P3VAUX), R91.2, R92.2, U22.8 (VCC)
VDDCML0_A: C26.2, C32.2, C38.2, L8.1, U11.40 (VDDCML0)
VDDCML0_B: C25.2, C31.2, C37.2, L7.1, U10.40 (VDDCML0)
VDDCML1_A: C4.2, C6.2, C10.2, L4.1, U11.31 (VDDCML1)
VDDCML1_B: C3.2, C5.2, C8.2, L3.1, U10.31 (VDDCML1)
VDDPLL_A: C49.2, C54.2, C59.2, L12.2, U11.45 (VDDPLL)
VDDPLL_B: C48.2, C53.2, C58.2, L11.2, U10.45 (VDDPLL)
VLINK_A: C28.2, C34.1, C84.2, L10.1, TP13.TP, U18.A1 (VOUT2), U18.B1 (VOUT2)
VLINK_B: C27.2, C33.1, C89.2, L9.1, TP14.TP, U18.D1 (VOUT1), U18.E1 (VOUT1)
VREF: C78.2, R74.2, U13.22 (VREF), U15.5 (VOUT)
V_PROTECT: C44.2, D6.2 (C), D7.2 (C), D8.2 (C), D9.C, R56.1, R61.1, TP5.TP

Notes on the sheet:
FMC
NB: Input protection voltage ~4.6V
L2 is the smallest package size I could find that barely meets current saturation requriements. An 8x8mm device that is probably safer is the Bourns SRN8040TA series.
Power: ~1.3A DC at 12V; 15.6W. With 90% efficiency regulation to 5.5V at serializer, this translates to 2.55A available, which is enough for 1A/LED + 500 mA serializer and FPGA.
JLCPCB 6 layer stackup: 1. Top Copper 0.035 mm P. Prepreg (2313*1) 0.1 mm 2. Inner Copper 0.0175 mm C. Core (Copper) 0.565 mm 3. Inner Copper 0.0175 mm P. Prepeg (2116*1) 0.127 mm 4. Inner Copper 0.0175 mm C. Core (Copper) 0.565 mm 5. Inner Copper 0.0175 mm P. Prepreg (2313*1) 0.1 mm 6. Bottom Copp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
DNP
NB: Use both MISO lines
NB: R-arrays provide input protection. Limit current thru internal clamp diodes to 10 mA at 20V.
NB: Worst case 100 mA draw from both ADC and DAC. With 10V stepdown, this is 1W dissipation.
ANALOG IO
CLK/TRIGGER I/0
NB: 3.16k = 12V output.
NB: VADJ must be set to 1.8V on host board!
NB: GA0 and GA1 define the LSBs of the EEPROM I2C address. We use 0x1010000
NB: FMC FRU module. Required by FMC standard.
Quad 1
Quad 2
Quad 3
NB: For best performance, quads should only be input or output, not mixtures.
TP1
TP2
TP3
TP4
TP5
NB: VLINK adjust. - Linear mode selected - R_AW = 0 : VLINK = 12V - R_AW = 5k : VLINK = 5.0V - General: VLINK = 36.24k/(3.16k + R_AW) + 0.6
NB: Default VBIAS = 1.65V
LINK A
LINK POWER
ANALOG POWER
LINK B
CLK IN 0
CLK IN 1
CLK OUT
FMC IO
HPC FMC
INTERNAL CLK/TRIG
SYNC
NB: Board address
NB: P,N order matches SDR datasheet spec.
NB: DC signals so no worries about DGND

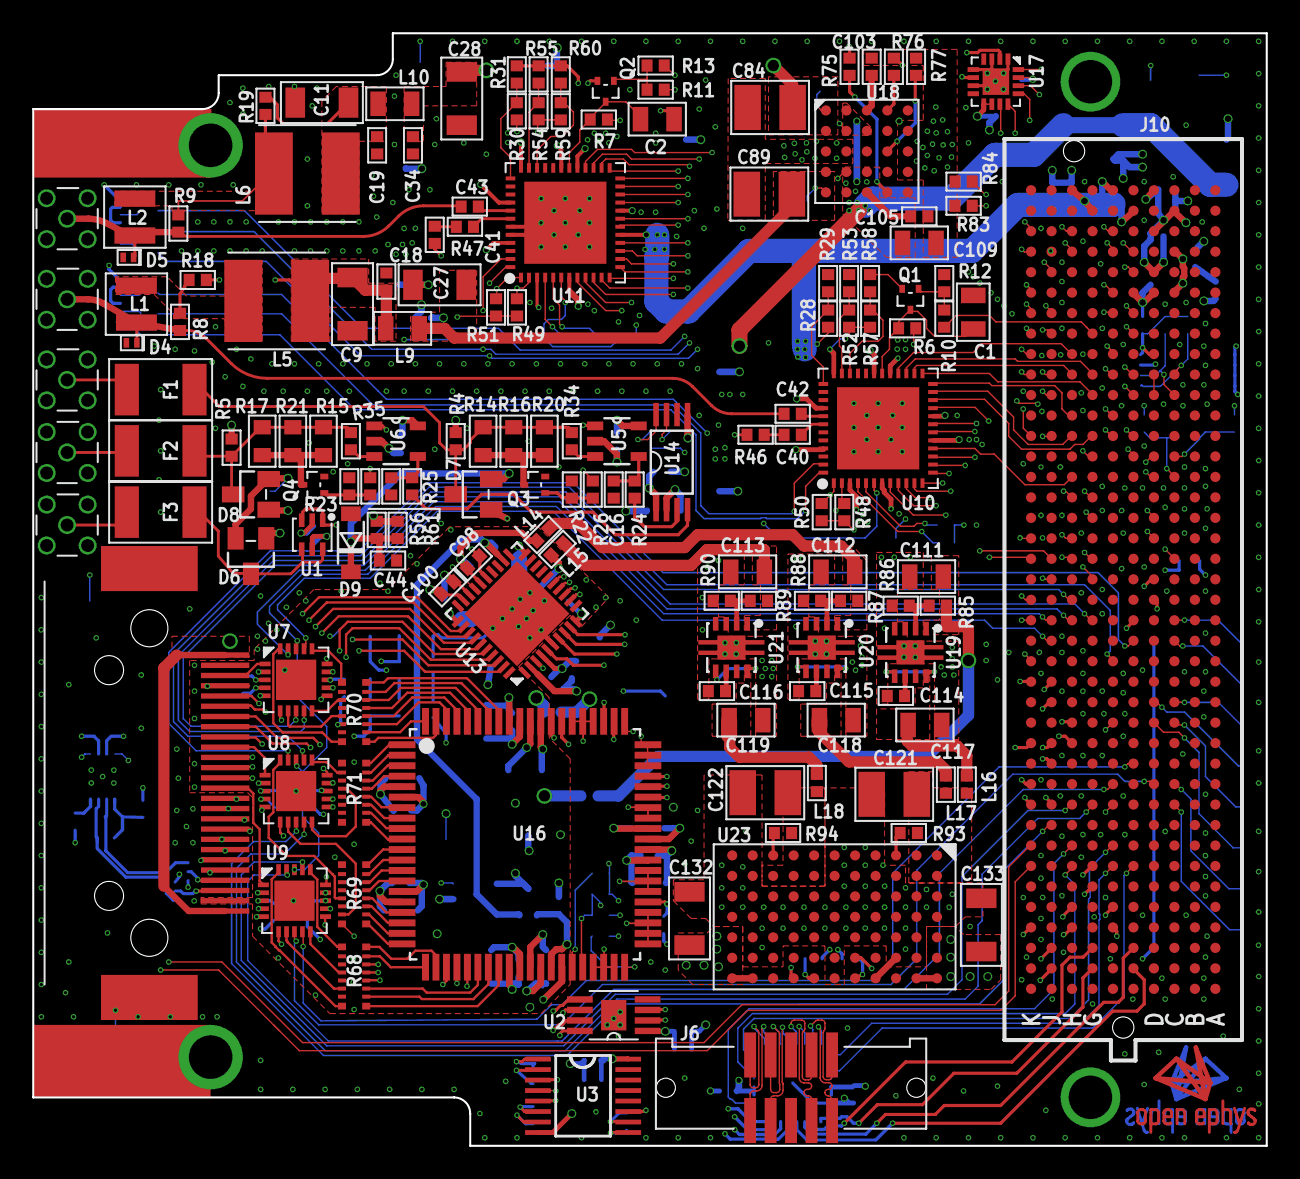
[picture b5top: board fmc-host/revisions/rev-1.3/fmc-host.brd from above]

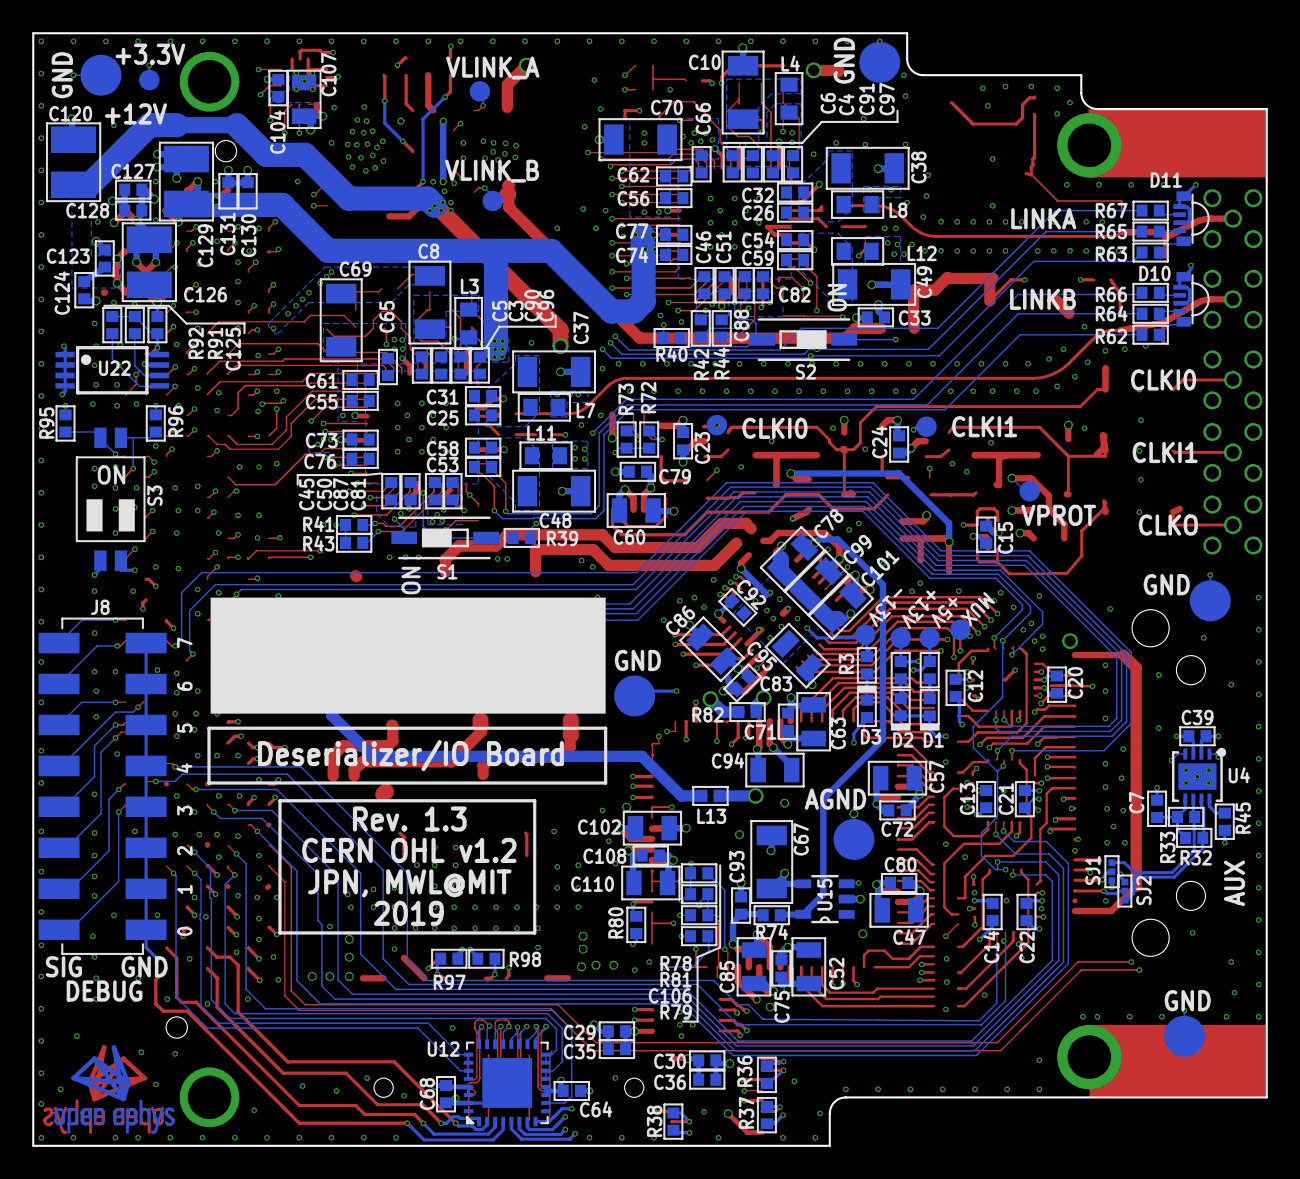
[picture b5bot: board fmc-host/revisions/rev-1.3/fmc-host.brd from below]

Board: 6 copper layers, 76.5 x 69.0 mm, 325 parts (173 on the bottom side), 321 nets.

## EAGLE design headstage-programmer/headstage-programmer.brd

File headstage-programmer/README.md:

# headstage-programmer
JTAG breakout for the [Intel USB Blaster
2](https://www.digikey.com/short/qqw7hm) used to program the headstages' MAX10
FPGA.

## Schematic

## Purpose
The dense layout required by the headstages in this repository makes exposing a
FPGA programming interface challenging. We have chosen to expose a JTAG
programming interface as a linear, 50 mil pitch array of small copper ["test
points"](https://en.wikipedia.org/wiki/Test_point). This programmer adapter
routes JTAG signals through a set of small ["pogo
pins"](https://en.wikipedia.org/wiki/Pogo_pin) that can reliably make a
temporary electrical connection with the test point array. Additionally, it
contains a AAA battery and boost converter to generate power for the headstage
during programming and to illuminate a white LED on the bottom of the board
that eases pogo-pin/test-point alignment.

## Gerber Files
{% include gerber_layers.md %}

## BOM
The BOM is located on [this google
sheet](https://docs.google.com/spreadsheets/d/1F-KWcdvH_63iXjZf0cgCfDiFX6XXW3qw6rlR8DZrFpQ/edit#gid=673969549).

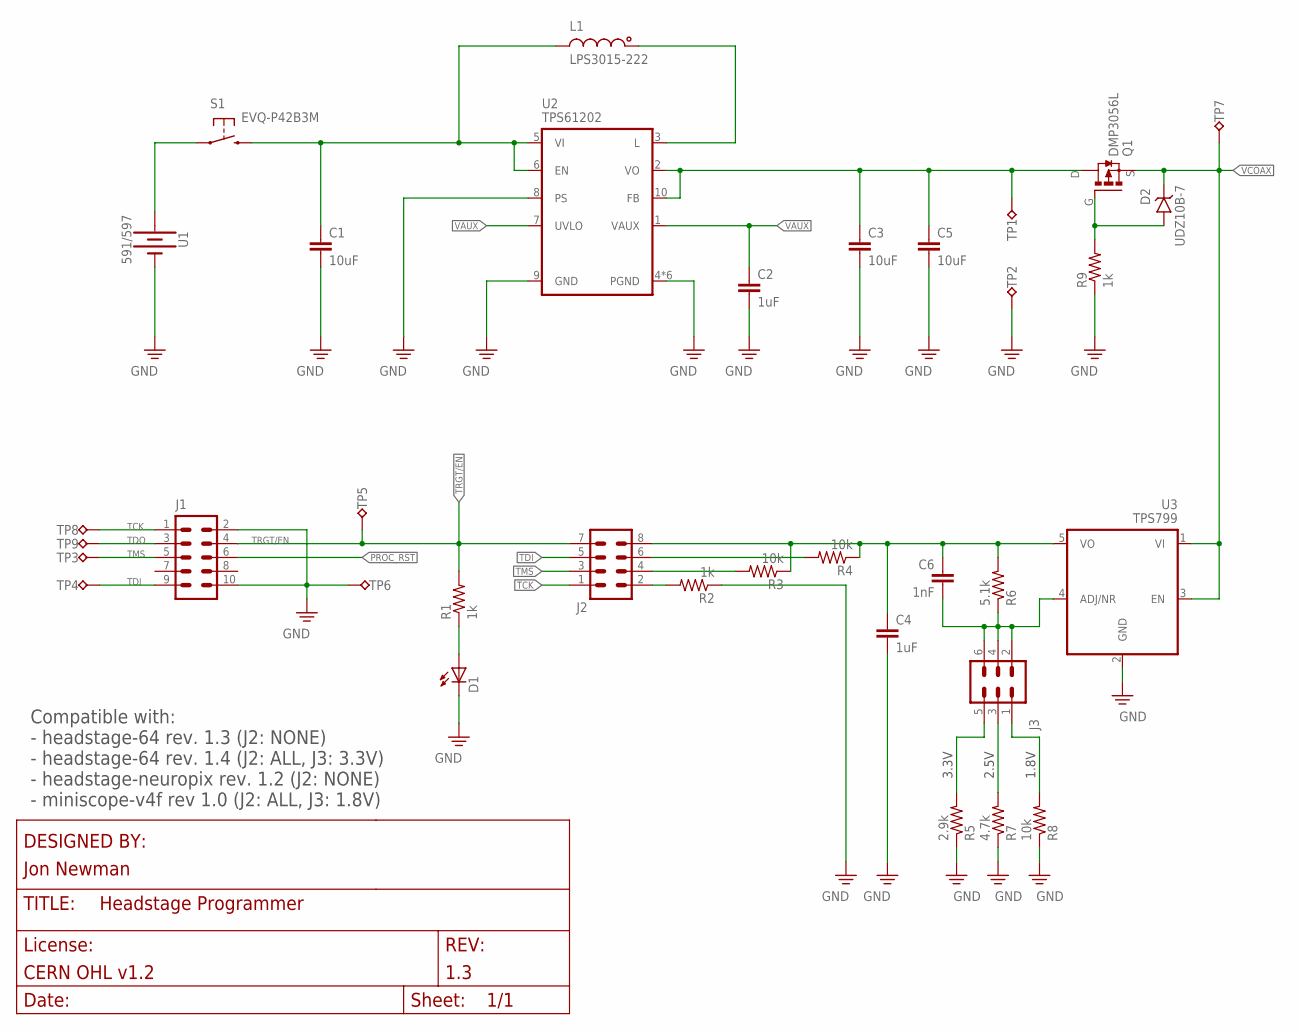
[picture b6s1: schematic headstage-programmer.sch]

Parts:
C1, C3, C5: 10uF; 0805
C2, C4: 1uF; 0603
C6: 1nF; 0402
D1: LED_0603; LED-0603
D2: UDZ10B-7; SOD-323; PARTNO UDZ10B-7
J1: 302-S101; 2X05_IDC
J2: PINHD-2X4_0.05"; 2X04-0.05"
J3: PINHD-2X3_0.05"; 2X03-0.05"
L1: LPS3015-222; LPS3015
Q1: DMP3056L; SOT23-GSD; PARTNO DMP3056L-7
R1, R2, R9: 1k; 0402
R3, R4, R8: 10k; 0402
R5: 2.9k; 0402
R6: 5.1k; 0402
R7: 4.7k; 0402
S1: EVQ-P42B3M; EVQP4
TP1, TP2: TP_1MM; TESTPOINT_1MM
TP3, TP4, TP5, TP6, TP7, TP8, TP9: TP_S500-6350-P2; POGO_S500-6350-P2
U1: 591/597; 597/591_AAA-HOLDER
U2: TPS61202; PWSON-N10+4-3X3
U3: TPS799; SOT-23-5

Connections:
GND: C1.2, C2.2, C3.2, C4.2, C5.2, D1.C, J1.2, J1.10, R2.1, R5.1, R7.1, R8.1, R9.1, TP2.1, TP6.P$1, U1.-1 (-), U1.-2 (-), U1.-3 (-), U2.4 (PGND), U2.8 (PS), U2.9 (GND), U2.PAD (PGND), U2.PAD1 (PGND), U2.PAD2 (PGND), U2.PAD3 (PGND), U2.PAD4 (PGND), U3.2 (GND); also elsewhere on the board
unnamed: D1.A, R1.1
unnamed: J2.2, R2.2
unnamed: L1.1, U2.3 (L)
unnamed: S1.1, U1.+1 (+), U1.+2 (+), U1.+3 (+)
unnamed: C6.2, J3.2, J3.4, J3.6, R6.1, U3.4 (ADJ/NR)
unnamed: J2.4, R3.2
unnamed: J3.1, R8.2
unnamed: J3.3, R7.2
unnamed: J3.5, R5.2
unnamed: J2.6, R4.2
unnamed: D2.A, Q1.G, R9.2
PROC_RST: J1.6
PWR: C3.1, C5.1, Q1.D, TP1.1, U2.2 (VO), U2.10 (FB)
TCK: J1.1, J2.1, TP8.P$1
TDI: J1.9, J2.5, TP4.P$1
TDO: J1.3, TP9.P$1
TMS: J1.5, J2.3, TP3.P$1
TRGT/EN: J1.4, J2.7, R1.2, TP5.P$1
VAUX: C2.1, U2.1 (VAUX), U2.7 (UVLO)
VCOAX: D2.C, Q1.S, TP7.P$1, U3.1 (VI), U3.3 (EN); also elsewhere on the board
VEN: C4.1, C6.1, J2.8, R3.1, R4.1, R6.2, U3.5 (VO)
VIN: C1.1, L1.2, S1.2 (S), U2.5 (VI), U2.6 (EN)

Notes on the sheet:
Compatible with: - headstage-64 rev. 1.3 (J2: NONE) - headstage-64 rev. 1.4 (J2: ALL, J3: 3.3V) - headstage-neuropix rev. 1.2 (J2: NONE) - miniscope-v4f rev 1.0 (J2: ALL, J3: 1.8V)
1.8V
2.5V
3.3V

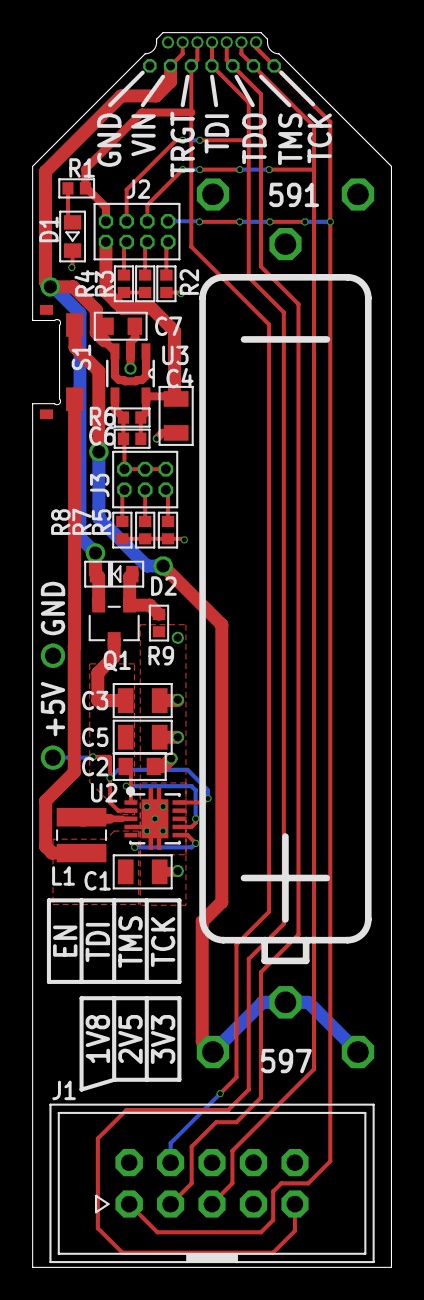
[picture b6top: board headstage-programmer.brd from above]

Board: 2 copper layers, 22.0 x 75.7 mm, 36 parts (0 on the bottom side), 22 nets.

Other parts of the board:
C7: 1uF; 0603

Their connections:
GND: C7.2; also elsewhere on the board
VCOAX: C7.1; also elsewhere on the board
